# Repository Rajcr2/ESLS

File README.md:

# Efficient Street Lighting System 

### Introduction

This was my academic project focused on creating a efficient LED based Street Lighting System which will avoid Power Wastage due to manual mismanagement.

### Motivation

I have observed many times that street lights were ON till 10 AM because operator forgot shut the main switch down and seen this very frequently & also lights were ON
1/2 hrs before SUNSET which leads to Power Wastage this is the Main reason or motivation behind this project.

### Objectives

1.	To make sure that all street lights will remain ON only during **DARK (Cloudy Condition)/NIGHT hours** & will remain off completely during **DAY HOURS (from Sunrise to Sunset)**.
2.	In case, If Power remains ON during Day-Time due to operators negligence LED lights will still remain OFF contributing to Energy saving.
3.	To Improve life of street light lamps.
4.	To Achieve Maximum Energy Efficiency. 

## System Design

### Components

| Component           | Purpose                             |
| -------------       | ----------------------------------- |
| **Arduino Nano**       | Microcontroller control unit        |
| **DS1307 - RTC Module** | Time scheduling                     |
| **MOC3021**             | Opto-isolated TRIAC driver          |
| **BT136 - TRIAC**       | AC load switching                   |
| **LDR Module**         | Detects ambient light intensity (luminance) |
| **470Ω Resistor**      | Limits current into optocoupler LED |

### Schematic Design

> The schematic is designed in KiCad. Schematic consists Arduino Nano (Control Unit), DS1307 RTC Module, optocoupler driver (MOC3021), BT136 TRIAC (switching circuit) for AC load along with Resistors.

### PCB Layout

> The PCB layout separates the low-voltage control circuitry from the AC power section to maintain electrical isolation. Routing was optimized to keep the power path short and reduce noise coupling.

### 3D View

### Design considerations

- **Isolation between low-voltage control circuit and AC mains section.**  
- **Clear routing of power paths for the TRIAC switching stage.**  
- **Through-hole components used for easier prototyping and soldering.**

## Circuit Simulation

### ngspice Simulation
**Transient analysis** was performed using ngspice integrated in KiCad to validate the Arduino driver stage.

> ### Limitation
> **Since microcontrollers cannot be simulated directly in SPICE, the Arduino PWM output was emulated using a pulse voltage source.**

- ### Simulated Circuit

- ### PWM Signal Emulation

All required Arduino PWM signals were emulated using the SPICE source :

Example : **PULSE(0 5 0 1u 1u 1m 2m)**
| Parameter    | Value |
| ------------ | ----- |
| Low Voltage  | 0 V   |
| High Voltage | 5 V   |
| Rise Time    | 1 µs |
| Fall Time    | 1 µs |
| ON Time      | 1 ms  |
| Period       | 2 ms  |

This results in a 50% duty cycle PWM signal, which corresponds to the Arduino command:

`analogWrite(pin,128)`

- ### Transient Analysis Results

The transient simulation produced the following waveform.

**Observations from the simulation** :
- The voltage waveform alternates between 0 V and 5 V, representing the PWM output.
- The current through the resistor and LED appears as periodic pulses synchronized with the PWM signal.

> **Calculation** :
>
> **I = (Vcc − Vf) / R**
>
> **Vcc** = 5 V, **Vf** ≈ 1.2 V (LED forward voltage), **R** = 470 Ω
>
> I ≈ (5 − 1.2) / 470
> 
> **I ≈ 8 mA**

- **The simulated current (~9.1 mA) aligns with this calculation and confirms that the Arduino output pin can safely drive the optocoupler input stage.**

### Proteus Simulation

To verify the embedded firmware behavior, the system was simulated in **Proteus**.

Unlike SPICE tools, Proteus allows simulation of **Arduino code execution along with peripheral modules such as the RTC**.

Simulation demonstrates and displays output Oscilloscope how the Arduino program changes the **output signal according to the RTC time conditions**.

### Simulation Outputs

- #### At Mid-Day Time :
  As per our goal light must remain off during Day Time and thats we have achieved. It will only **"Turn ON"** if LDR triggers due to cloudy condition.

- #### At Evening Time :
  As during sunset time, we need light but, not fully in regular seasons so, 50% light is enough and that we got it. For special case, during cloudy conditions if it senses Darkness around will trigger LDR. so, Both scenarios are covered.

- #### At Night :
  Light is fully ON.

- #### At Early Morning :

- #### At Morning

These results confirm that the firmware correctly generates the expected control signal based on RTC timing conditions. Using the same logic then implemented and validated on the physical hardware prototype.
__________
## Hardware Implementation

The circuit is implemented on a custom PCB designed in KiCad. 
The circuit board includes the Arduino Nano module, RTC module, LDR sensor module, MOC3021 optocoupler, 470Ω resistor, connectors, and a BT136 TRIAC.

The Arduino Nano is mounted on the PCB and programmed to execute the control logic based on RTC timing conditions. After assembling the PCB, the logic was tested on a working prototype to validate the system behaviour of the control stage.

### PCB

### Prototype

## Results

**The hardware prototype was tested at different time conditions defined in the firmware.
The observed outputs confirm that the system correctly generates the control signal and operates as intended.**

- #### 1. During Day Time
  Mechanism is developed in way that during hours from **8 AM to 6 PM** Light will remain OFF. In case, operator forgot to switch off main switch still lights will be OFF.

- #### 2. At Evening
  In the evening, during the time of **Sunset** there is enough light present so, we don't need street lights with Full intensity, so we have make   sure that lights will be ON with bit less intensity like at **6-7 PM = 40%** & **7-8 PM = 50%**. Same logic is used during **Sunrise** time as well. 

- #### 3. At Peak Night Hours
  Only During complete DARK hours mainly from **8 PM to 5 AM** Lights will be ON with Full intensity.

- #### 4. During Cloudy Conditions
  This is a special case designed for Rainy Season, where if clouds appear in Day hours incase if LDR senses surrounding is DARK it will Turn ON lights Automatically without any need Manual workers risking their life in Rainy times.

## Conclusion
Developed a system that will use **RTC (Real Time Clock) and surrounding ambience with LDR Sensor** intelligently and will make sure Light will be **ON only during DARK Hours** in case of **DAY Hours it will be ON but, with less intensity**. Which will,
- **Improve life of Street Lights.**
- **Contribute to lot of Energy Savings.**

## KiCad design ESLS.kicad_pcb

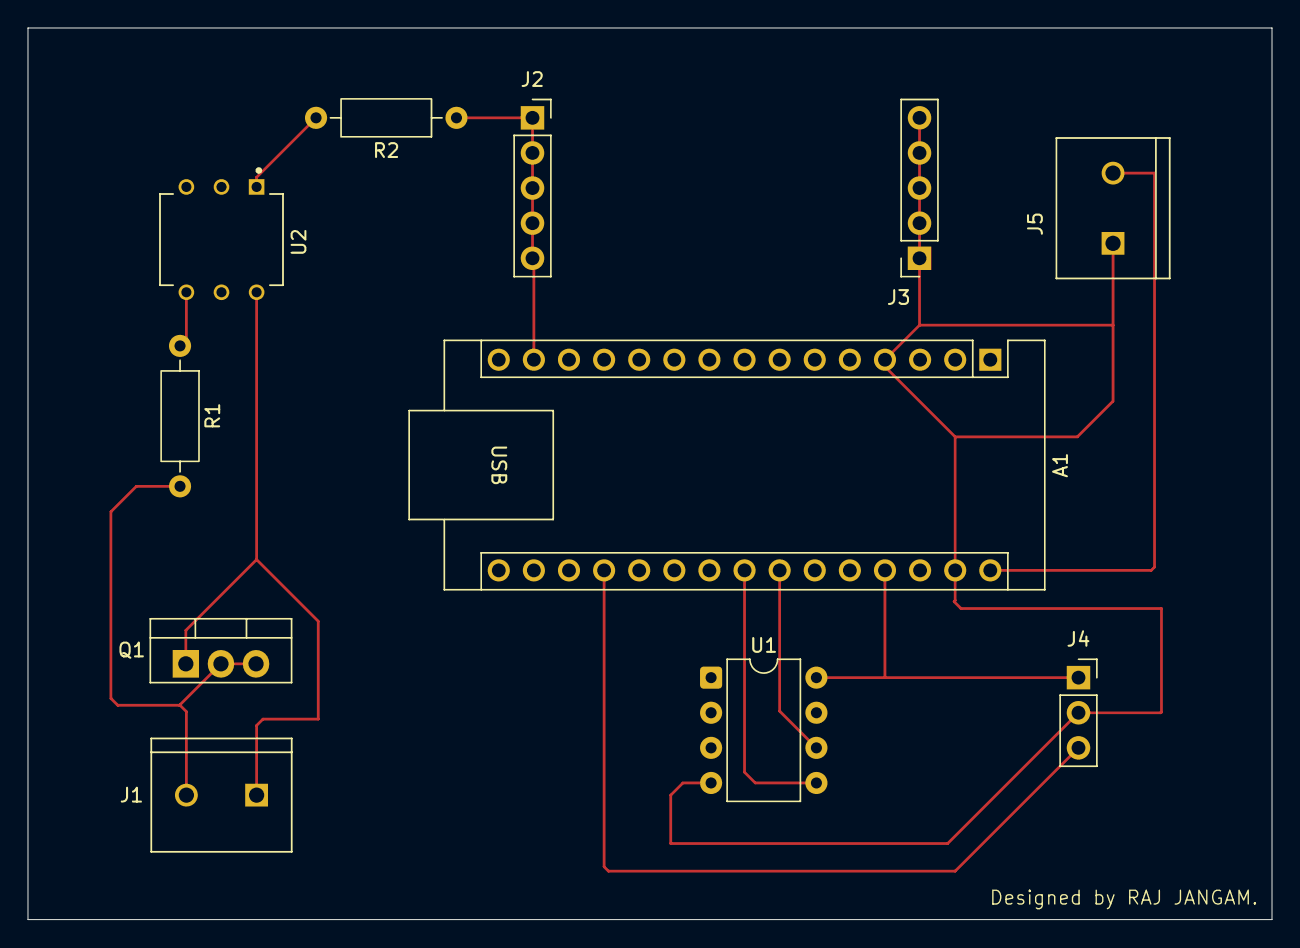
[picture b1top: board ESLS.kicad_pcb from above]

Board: 2 copper layers, 90.0 x 64.5 mm, 11 parts (0 on the bottom side), 11 nets.

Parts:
A1: Arduino_Nano_v3.x; Arduino_Nano
J1, J5: Screw_Terminal_01x02; TE_282837-2
J2, J3: Conn_01x05_Socket; PinSocket_1x05_P2.54mm_Vertical
J4: Conn_01x03_Socket; PinSocket_1x03_P2.54mm_Vertical
Q1: BT136-600; TO-220-3_Vertical
R1, R2: 470; R_Axial_DIN0207_L6.3mm_D2.5mm_P10.16mm_Horizontal
U1: DS1307+; DIP-8_W7.62mm
U2: MOC3021M; DIP762W45P254L889H508Q6_MOC3021

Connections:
GND: A1.4 (GND), A1.29 (GND), J3.1, J3.2, J3.3, J3.4, J3.5, J4.2, J5.1, U1.4 (GND)
unnamed: A1.27 (+5V), J4.1, U1.8 (VCC)
unnamed: A1.19 (A0), J4.3
unnamed: A1.23 (A4), U1.5 (SDA)
unnamed: A1.24 (A5), U1.6 (SCL)
unnamed: A1.14 (D11), J2.1, J2.2, J2.3, J2.4, J2.5, R2.1
unnamed: A1.30 (VIN), J5.2
unnamed: J1.1, Q1.1 (A1), U2.6
unnamed: J1.2, Q1.2 (A2), Q1.3 (G), R1.2
unnamed: R1.1, U2.4
unnamed: R2.2, U2.1

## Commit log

2026-03-16 Create h
2026-03-16 Create f
